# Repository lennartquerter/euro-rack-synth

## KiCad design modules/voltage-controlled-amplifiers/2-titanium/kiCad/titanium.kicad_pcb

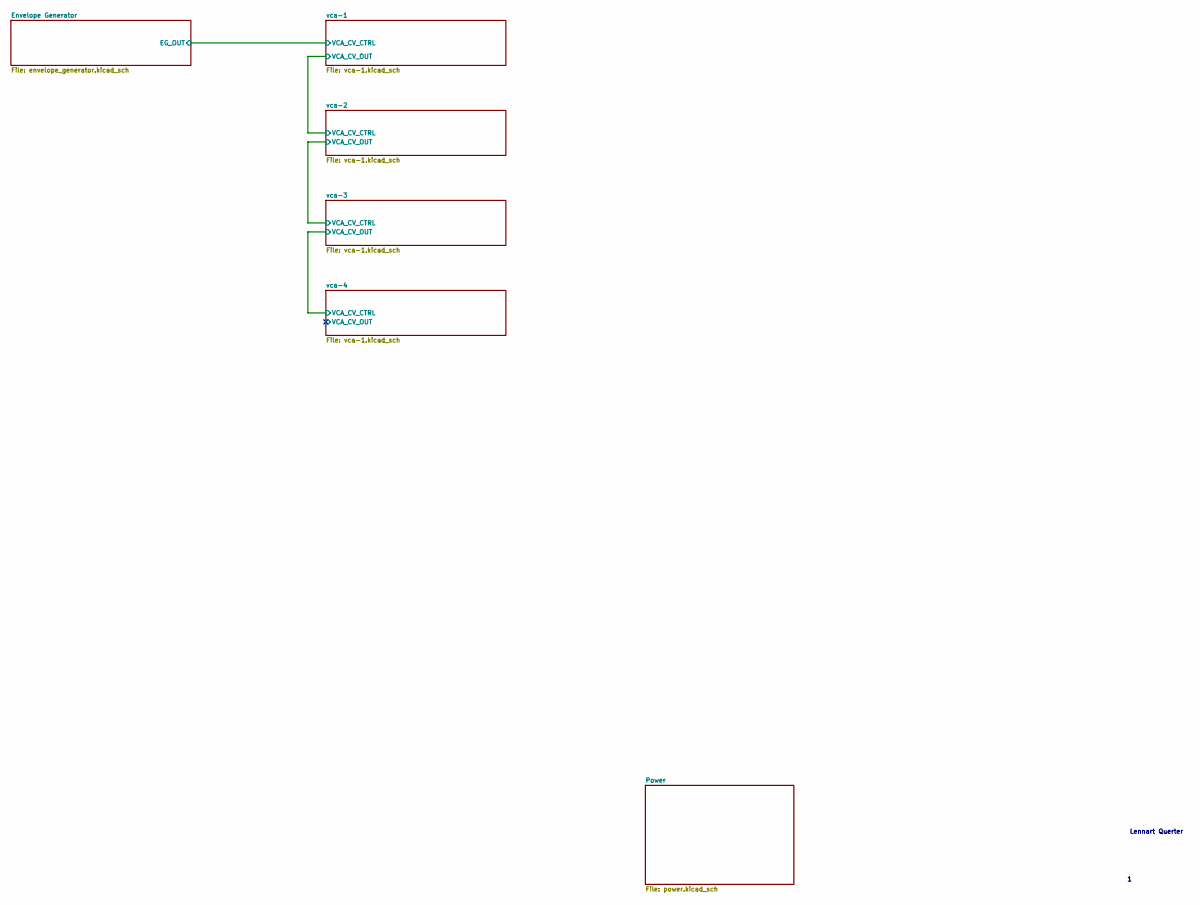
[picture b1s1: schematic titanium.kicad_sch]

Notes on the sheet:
Lennart Querter

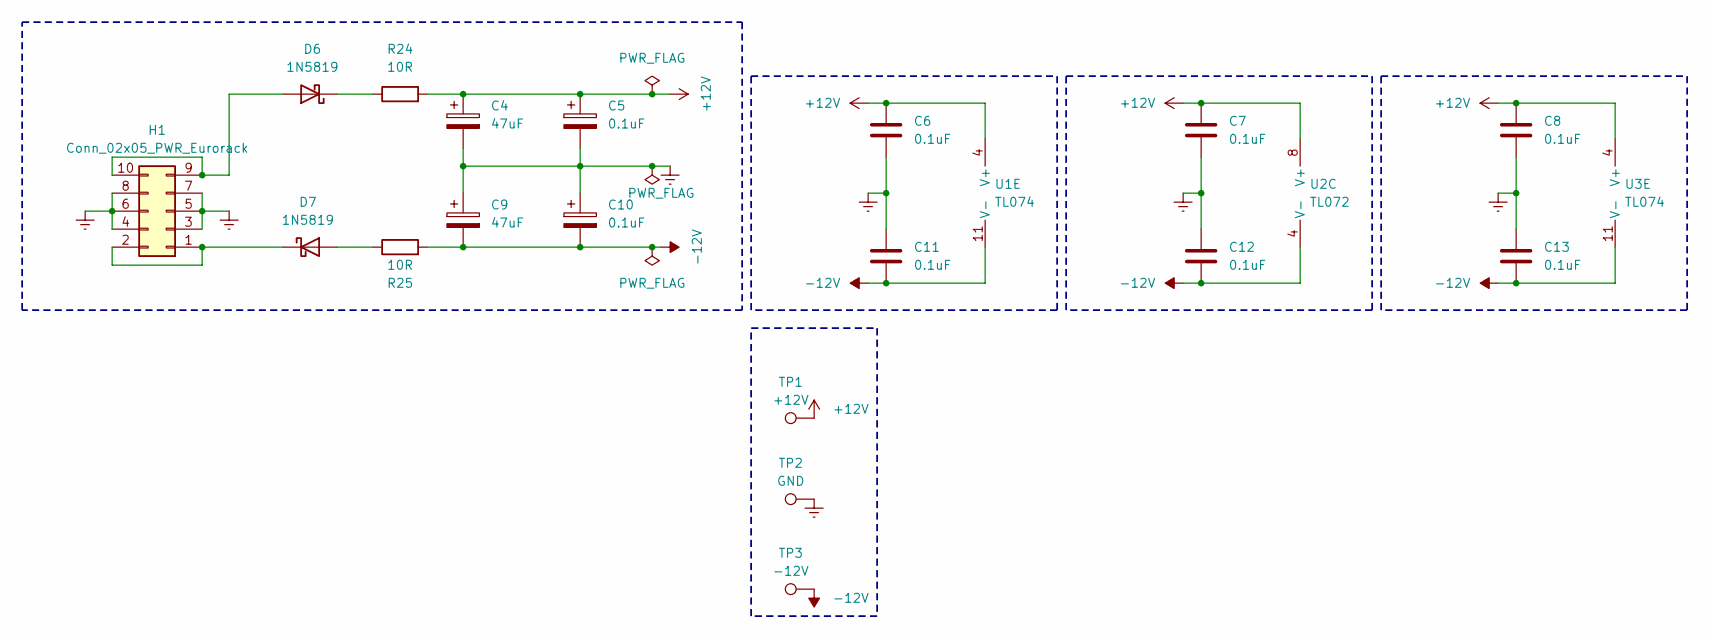
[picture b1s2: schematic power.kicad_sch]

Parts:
C4, C9: 47uF; CP_Radial_D6.3mm_P2.50mm
C5, C10: 0.1uF; CP_Radial_D4.0mm_P2.00mm
C6, C7, C8, C11, C12, C13: 0.1uF; C_0805_2012Metric_Pad1.18x1.45mm_HandSolder
D6, D7: 1N5819; D_SOD-123
H1: Conn_02x05_PWR_Eurorack; IDC-Header_2x05_P2.54mm_Vertical
R24, R25: 10R; R_0805_2012Metric_Pad1.20x1.40mm_HandSolder
TP1: +12V; Pin_D1.0mm_L10.0mm
TP2: GND; Pin_D1.0mm_L10.0mm
TP3: -12V; Pin_D1.0mm_L10.0mm
U1, U3: TL074; SOIC-14
U2: TL072; SOIC-8

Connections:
+12V: C4.1, C5.1, C6.1, C7.1, C8.1, R24.2, TP1.1, U1.4 (V+), U2.8 (V+), U3.4 (V+); also elsewhere on the board
-12V: C9.2, C10.2, C11.2, C12.2, C13.2, R25.2, TP3.1, U1.11 (V-), U2.4 (V-), U3.11 (V-); also elsewhere on the board
GNDREF: C4.2, C5.2, C6.2, C7.2, C8.2, C9.1, C10.1, C11.1, C12.1, C13.1, H1.3, H1.4, H1.5, H1.6, H1.7, H1.8, TP2.1, U1.12 (+), U3.3 (+); also elsewhere on the board
unnamed: D6.2 (A), H1.9, H1.10
unnamed: D6.1 (K), R24.1
unnamed: D7.2 (A), R25.1
unnamed: D7.1 (K), H1.1, H1.2
unnamed 64: U1.1; also elsewhere on the board
unnamed 66: U1.14; also elsewhere on the board
unnamed 70: U3.14; also elsewhere on the board
unnamed 72: U3.1; also elsewhere on the board
unnamed 76: U1.3 (+); also elsewhere on the board
unnamed 77: U1.2 (-); also elsewhere on the board
unnamed 81: U1.13 (-); also elsewhere on the board
unnamed 83: U3.2 (-); also elsewhere on the board
unnamed 87: U3.12 (+); also elsewhere on the board
unnamed 88: U3.13 (-); also elsewhere on the board

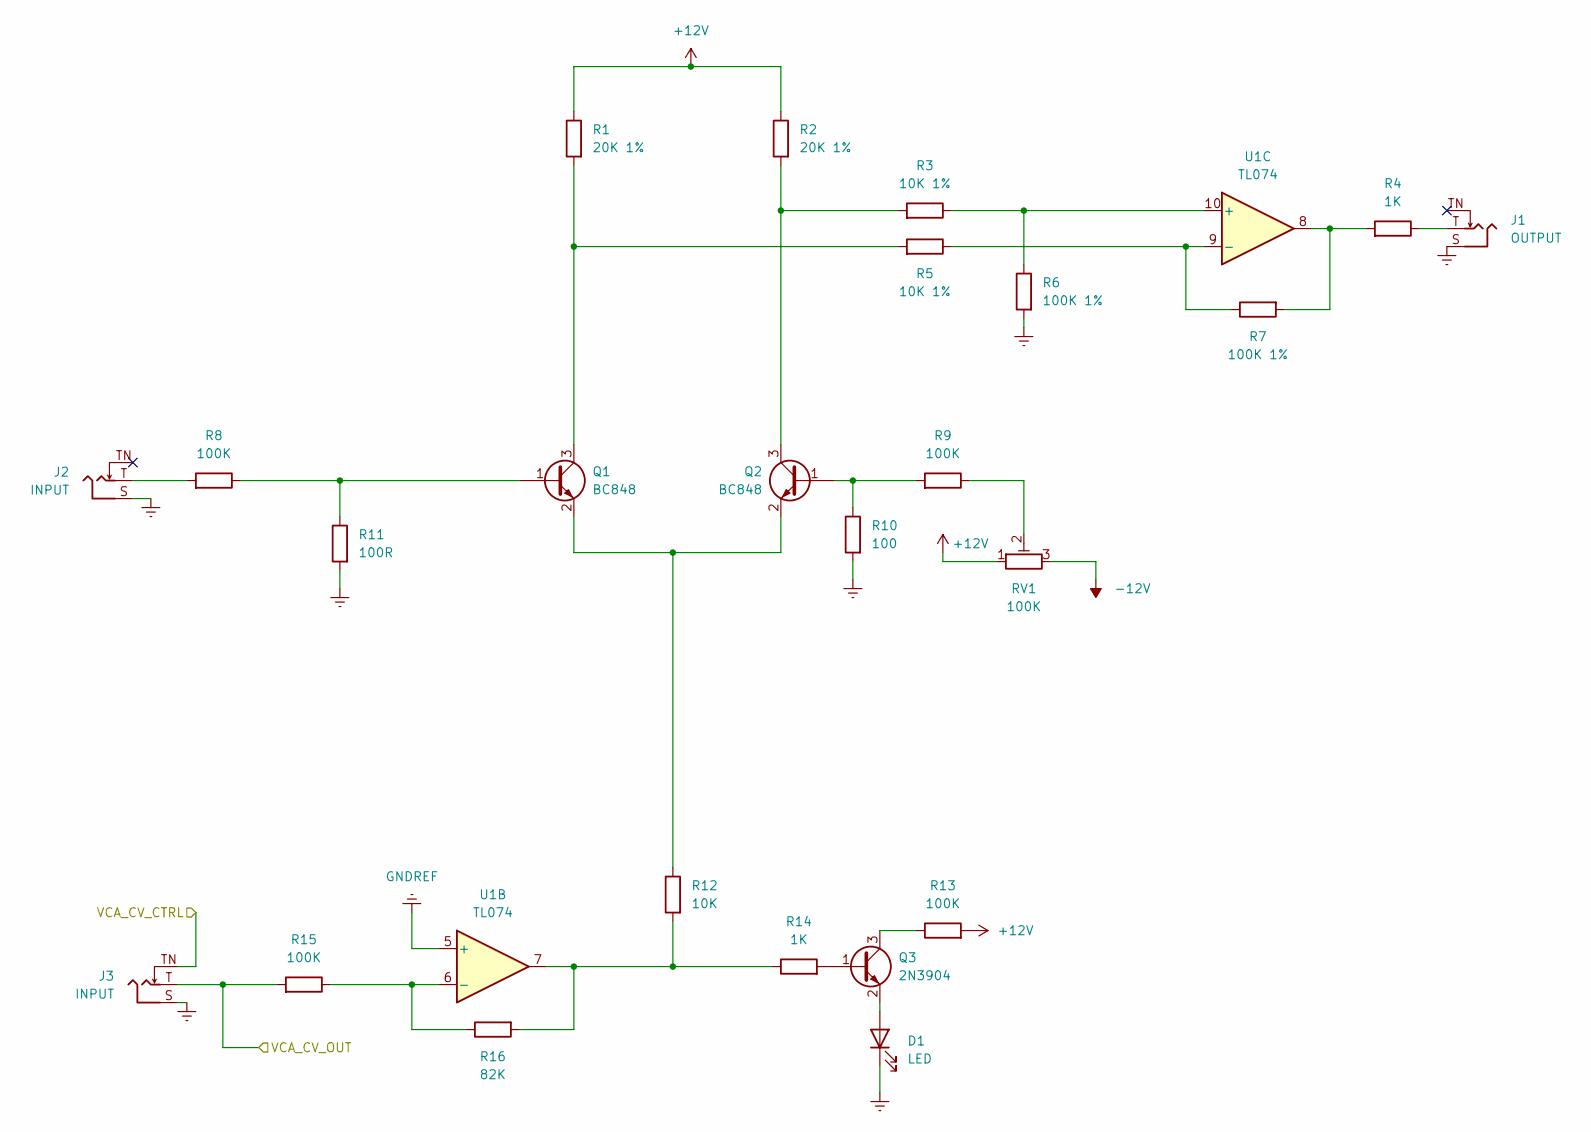
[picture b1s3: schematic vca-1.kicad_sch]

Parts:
D1: LED; LED_D3.0mm
J1: OUTPUT; Jack_3.5mm_QingPu_WQP-PJ398SM_Vertical_CircularHoles
J2, J3: INPUT; Jack_3.5mm_QingPu_WQP-PJ398SM_Vertical_CircularHoles
Q1, Q2: BC848; SOT-23_Handsoldering
Q3: 2N3904; SOT-23_Handsoldering
R1, R2: 20K 1%; R_0805_2012Metric_Pad1.20x1.40mm_HandSolder
R3, R5: 10K 1%; R_0805_2012Metric_Pad1.20x1.40mm_HandSolder
R4, R14: 1K; R_0805_2012Metric_Pad1.20x1.40mm_HandSolder
R6, R7: 100K 1%; R_0805_2012Metric_Pad1.20x1.40mm_HandSolder
R8, R9, R13, R15: 100K; R_0805_2012Metric_Pad1.20x1.40mm_HandSolder
R10: 100; R_0805_2012Metric_Pad1.20x1.40mm_HandSolder
R11: 100R; R_0805_2012Metric_Pad1.20x1.40mm_HandSolder
R12: 10K; R_0805_2012Metric_Pad1.20x1.40mm_HandSolder
R16: 82K; R_0805_2012Metric_Pad1.20x1.40mm_HandSolder
RV1: 100K; Potentiometer_Piher_PT-6-V_Vertical
U1: TL074; SOIC-14

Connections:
+12V: R1.2, R2.2, R13.2, RV1.1; also elsewhere on the board
-12V: RV1.3; also elsewhere on the board
/Envelope Generator/EG_OUT: J3.TN; also elsewhere on the board
/vca-1/VCA_CV_OUT: J3.T, R15.1; also elsewhere on the board
GNDREF: D1.1 (K), J1.S, J2.S, J3.S, R6.1, R10.1, R11.1, U1.5 (+), U1.12 (+); also elsewhere on the board
unnamed: D1.2 (A), Q3.2 (E)
unnamed: J1.T, R4.2
unnamed: J2.T, R8.1
unnamed: Q1.1 (B), R8.2, R11.2
unnamed: Q1.3 (C), R1.1, R5.1
unnamed: Q1.2 (E), Q2.2 (E), R12.2
unnamed: Q2.1 (B), R9.1, R10.2
unnamed: Q2.3 (C), R2.1, R3.1
unnamed: Q3.1 (B), R14.2
unnamed: Q3.3 (C), R13.1
unnamed: R4.1, R7.1, U1.8
unnamed: R9.2, RV1.2
unnamed: R12.1, R14.1, R16.1, U1.7
unnamed 64: U1.1; also elsewhere on the board
unnamed 66: U1.14; also elsewhere on the board
unnamed 76: U1.3 (+); also elsewhere on the board
unnamed 77: U1.2 (-); also elsewhere on the board
unnamed: R15.2, R16.2, U1.6 (-)
unnamed: R3.2, R6.2, U1.10 (+)
unnamed: R5.2, R7.2, U1.9 (-)
unnamed 81: U1.13 (-); also elsewhere on the board

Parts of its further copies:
D8, D9, D10: LED; LED_D3.0mm
J6, J9, J12: OUTPUT; Jack_3.5mm_QingPu_WQP-PJ398SM_Vertical_CircularHoles
J7, J8, J10, J11, J13, J14: INPUT; Jack_3.5mm_QingPu_WQP-PJ398SM_Vertical_CircularHoles
Q5, Q6, Q8, Q9, Q11, Q12: BC848; SOT-23_Handsoldering
Q7, Q10, Q13: 2N3904; SOT-23_Handsoldering
R26, R27, R42, R43, R58, R59: 20K 1%; R_0805_2012Metric_Pad1.20x1.40mm_HandSolder
R28, R30, R44, R46, R60, R62: 10K 1%; R_0805_2012Metric_Pad1.20x1.40mm_HandSolder
R29, R39, R45, R55, R61, R71: 1K; R_0805_2012Metric_Pad1.20x1.40mm_HandSolder
R31, R32, R47, R48, R63, R64: 100K 1%; R_0805_2012Metric_Pad1.20x1.40mm_HandSolder
R33, R34, R38, R40, R49, R50, R54, R56, R65, R66, R70, R72: 100K; R_0805_2012Metric_Pad1.20x1.40mm_HandSolder
R35, R51, R67: 100; R_0805_2012Metric_Pad1.20x1.40mm_HandSolder
R36, R52, R68: 100R; R_0805_2012Metric_Pad1.20x1.40mm_HandSolder
R37, R53, R69: 10K; R_0805_2012Metric_Pad1.20x1.40mm_HandSolder
R41, R57, R73: 82K; R_0805_2012Metric_Pad1.20x1.40mm_HandSolder
RV2, RV3, RV4: 100K; Potentiometer_Piher_PT-6-V_Vertical

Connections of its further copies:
+12V: R26.2, R27.2, R38.2, R42.2, R43.2, R54.2, R58.2, R59.2, R70.2, RV2.1, RV3.1, RV4.1; also elsewhere on the board
-12V: RV2.3, RV3.3, RV4.3; also elsewhere on the board
/vca-1/VCA_CV_OUT: J8.TN; also elsewhere on the board
/vca-2/VCA_CV_OUT: J8.T, J11.TN, R40.1
/vca-3/VCA_CV_OUT: J11.T, J14.TN, R56.1
/vca-4/VCA_CV_OUT: J14.T, R72.1
GNDREF: D8.1 (K), D9.1 (K), D10.1 (K), J6.S, J7.S, J8.S, J9.S, J10.S, J11.S, J12.S, J13.S, J14.S, R31.1, R35.1, R36.1, R47.1, R51.1, R52.1, R63.1, R67.1, R68.1; also elsewhere on the board
unnamed: D8.2 (A), Q7.2 (E)
unnamed: D9.2 (A), Q10.2 (E)
unnamed: D10.2 (A), Q13.2 (E)
unnamed: J6.T, R29.2
unnamed: J7.T, R33.1
unnamed: J9.T, R45.2
unnamed: J10.T, R49.1
unnamed: J12.T, R61.2
unnamed: J13.T, R65.1
unnamed: Q5.1 (B), R33.2, R36.2
unnamed: Q5.3 (C), R26.1, R30.1
unnamed: Q5.2 (E), Q6.2 (E), R37.2
unnamed: Q6.1 (B), R34.1, R35.2
unnamed: Q6.3 (C), R27.1, R28.1
unnamed: Q7.1 (B), R39.2
unnamed: Q7.3 (C), R38.1
unnamed: Q8.1 (B), R49.2, R52.2
unnamed: Q8.3 (C), R42.1, R46.1
unnamed: Q8.2 (E), Q9.2 (E), R53.2
unnamed: Q9.1 (B), R50.1, R51.2
unnamed: Q9.3 (C), R43.1, R44.1
unnamed: Q10.1 (B), R55.2
unnamed: Q10.3 (C), R54.1
unnamed: Q11.1 (B), R65.2, R68.2
unnamed: Q11.3 (C), R58.1, R62.1
unnamed: Q11.2 (E), Q12.2 (E), R69.2
unnamed: Q12.1 (B), R66.1, R67.2
unnamed: Q12.3 (C), R59.1, R60.1
unnamed: Q13.1 (B), R71.2
unnamed: Q13.3 (C), R70.1
unnamed 64: R29.1, R32.1; also elsewhere on the board
unnamed: R34.2, RV2.2
unnamed 66: R37.1, R39.1, R41.1; also elsewhere on the board
unnamed 67: R45.1, R48.1; also elsewhere on the board
unnamed: R50.2, RV3.2
unnamed 69: R53.1, R55.1, R57.1; also elsewhere on the board
unnamed 70: R61.1, R64.1; also elsewhere on the board
unnamed: R66.2, RV4.2
unnamed 72: R69.1, R71.1, R73.1; also elsewhere on the board
unnamed 76: R28.2, R31.2; also elsewhere on the board
unnamed 77: R30.2, R32.2; also elsewhere on the board
unnamed 81: R40.2, R41.2; also elsewhere on the board
unnamed 83: R72.2, R73.2; also elsewhere on the board
unnamed 84: R56.2, R57.2; also elsewhere on the board
unnamed 85: R44.2, R47.2; also elsewhere on the board
unnamed 86: R46.2, R48.2; also elsewhere on the board
unnamed 87: R60.2, R63.2; also elsewhere on the board
unnamed 88: R62.2, R64.2; also elsewhere on the board

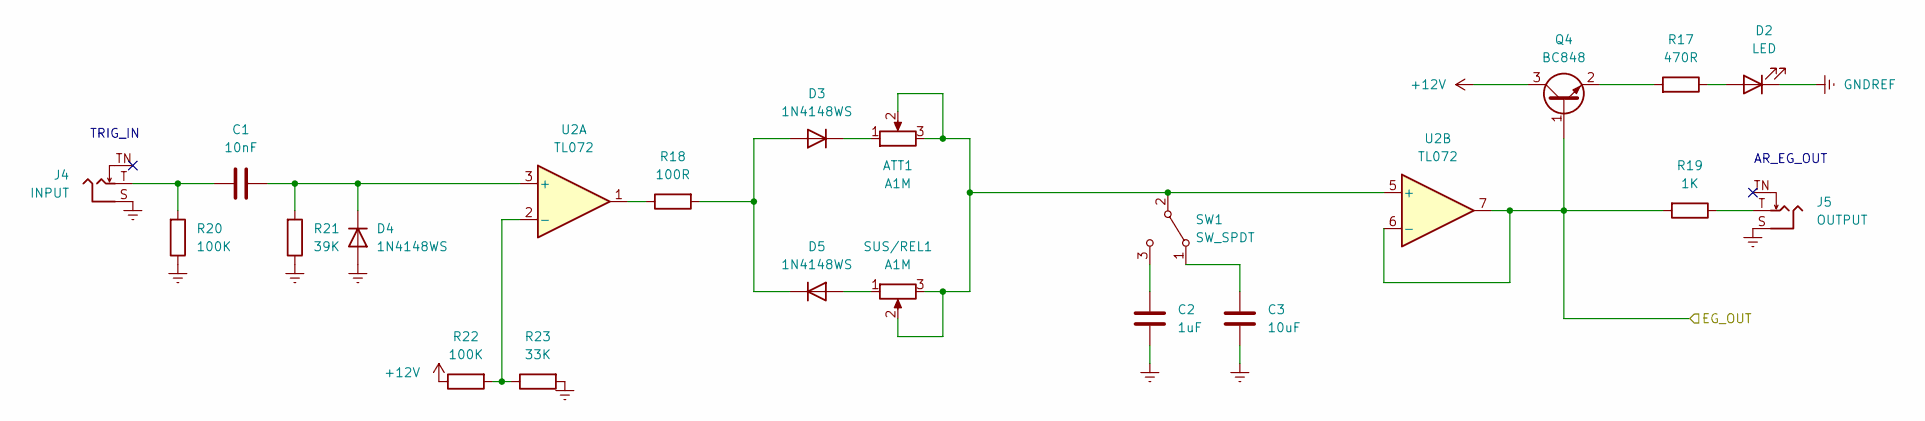
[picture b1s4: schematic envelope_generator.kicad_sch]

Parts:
ATT1: A1M; Potentiometer_TT_P0915N
C1: 10nF; C_0805_2012Metric_Pad1.18x1.45mm_HandSolder
C2: 1uF; C_RECT_WIMA_0.1uF
C3: 10uF; C_RECT_MKT_1uF
D2: LED; LED_D3.0mm
D3, D4, D5: 1N4148WS; D_SOD-323_HandSoldering
J4: INPUT; Jack_3.5mm_QingPu_WQP-PJ398SM_Vertical_CircularHoles
J5: OUTPUT; Jack_3.5mm_QingPu_WQP-PJ398SM_Vertical_CircularHoles
Q4: BC848; SOT-23_Handsoldering
R17: 470R; R_0805_2012Metric_Pad1.20x1.40mm_HandSolder
R18: 100R; R_0805_2012Metric_Pad1.20x1.40mm_HandSolder
R19: 1K; R_0805_2012Metric_Pad1.20x1.40mm_HandSolder
R20, R22: 100K; R_0805_2012Metric_Pad1.20x1.40mm_HandSolder
R21: 39K; R_0805_2012Metric_Pad1.20x1.40mm_HandSolder
R23: 33K; R_0805_2012Metric_Pad1.20x1.40mm_HandSolder
SUS/REL1: A1M; Potentiometer_TT_P0915N
SW1: SW_SPDT; SW_default
U2: TL072; SOIC-8

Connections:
+12V: Q4.3 (C), R22.2; also elsewhere on the board
/Envelope Generator/EG_OUT: Q4.1 (B), R19.1, U2.6 (-), U2.7; also elsewhere on the board
GNDREF: C2.2, C3.2, D2.1 (K), D4.2 (A), J4.S, J5.S, R20.2, R21.2, R23.1; also elsewhere on the board
unnamed: C1.1, J4.T, R20.1
unnamed: D2.2 (A), R17.2
unnamed: D3.2 (A), D5.1 (K), R18.1
unnamed: ATT1.1, D3.1 (K)
unnamed: C1.2, D4.1 (K), R21.1, U2.3 (+)
unnamed: D5.2 (A), SUS/REL1.1
unnamed: J5.T, R19.2
unnamed: Q4.2 (E), R17.1
unnamed: R18.2, U2.1
unnamed: C3.1, SW1.1 (A)
unnamed: ATT1.2, ATT1.3, SUS/REL1.2, SUS/REL1.3, SW1.2 (B), U2.5 (+)
unnamed: C2.1, SW1.3 (C)
unnamed: R22.1, R23.2, U2.2 (-)

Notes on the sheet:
AR_EG_OUT
TRIG_IN

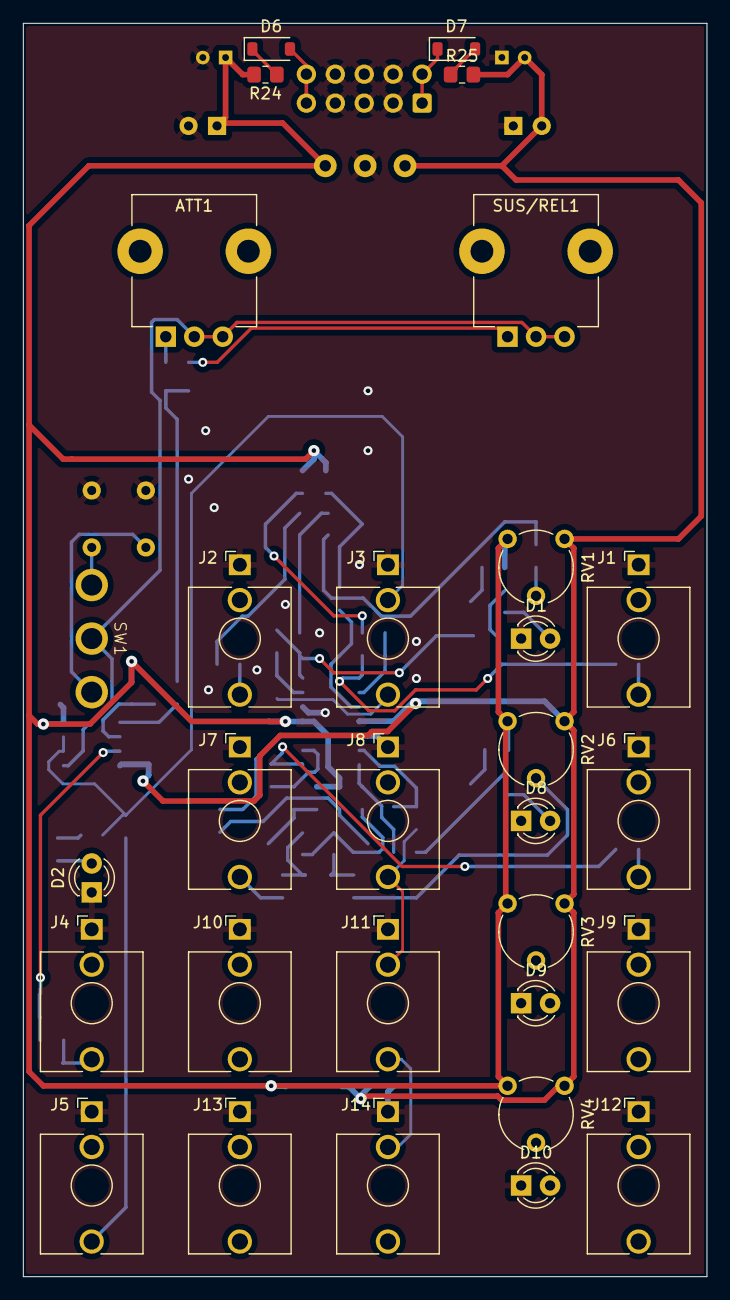
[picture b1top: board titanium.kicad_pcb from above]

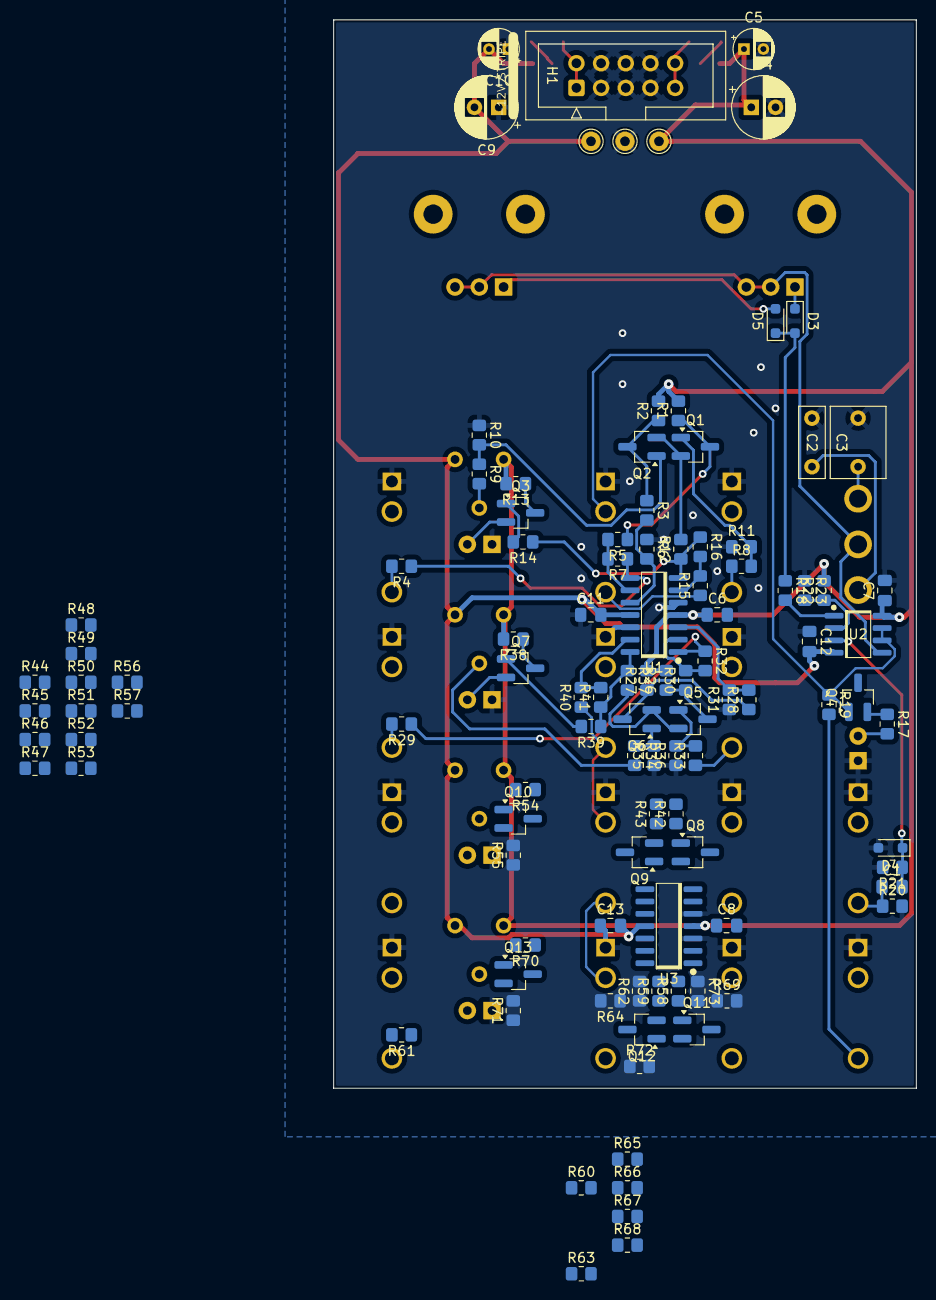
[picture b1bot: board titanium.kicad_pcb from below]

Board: 2 copper layers, 60.0 x 110.0 mm, 137 parts (107 on the bottom side), 89 nets.

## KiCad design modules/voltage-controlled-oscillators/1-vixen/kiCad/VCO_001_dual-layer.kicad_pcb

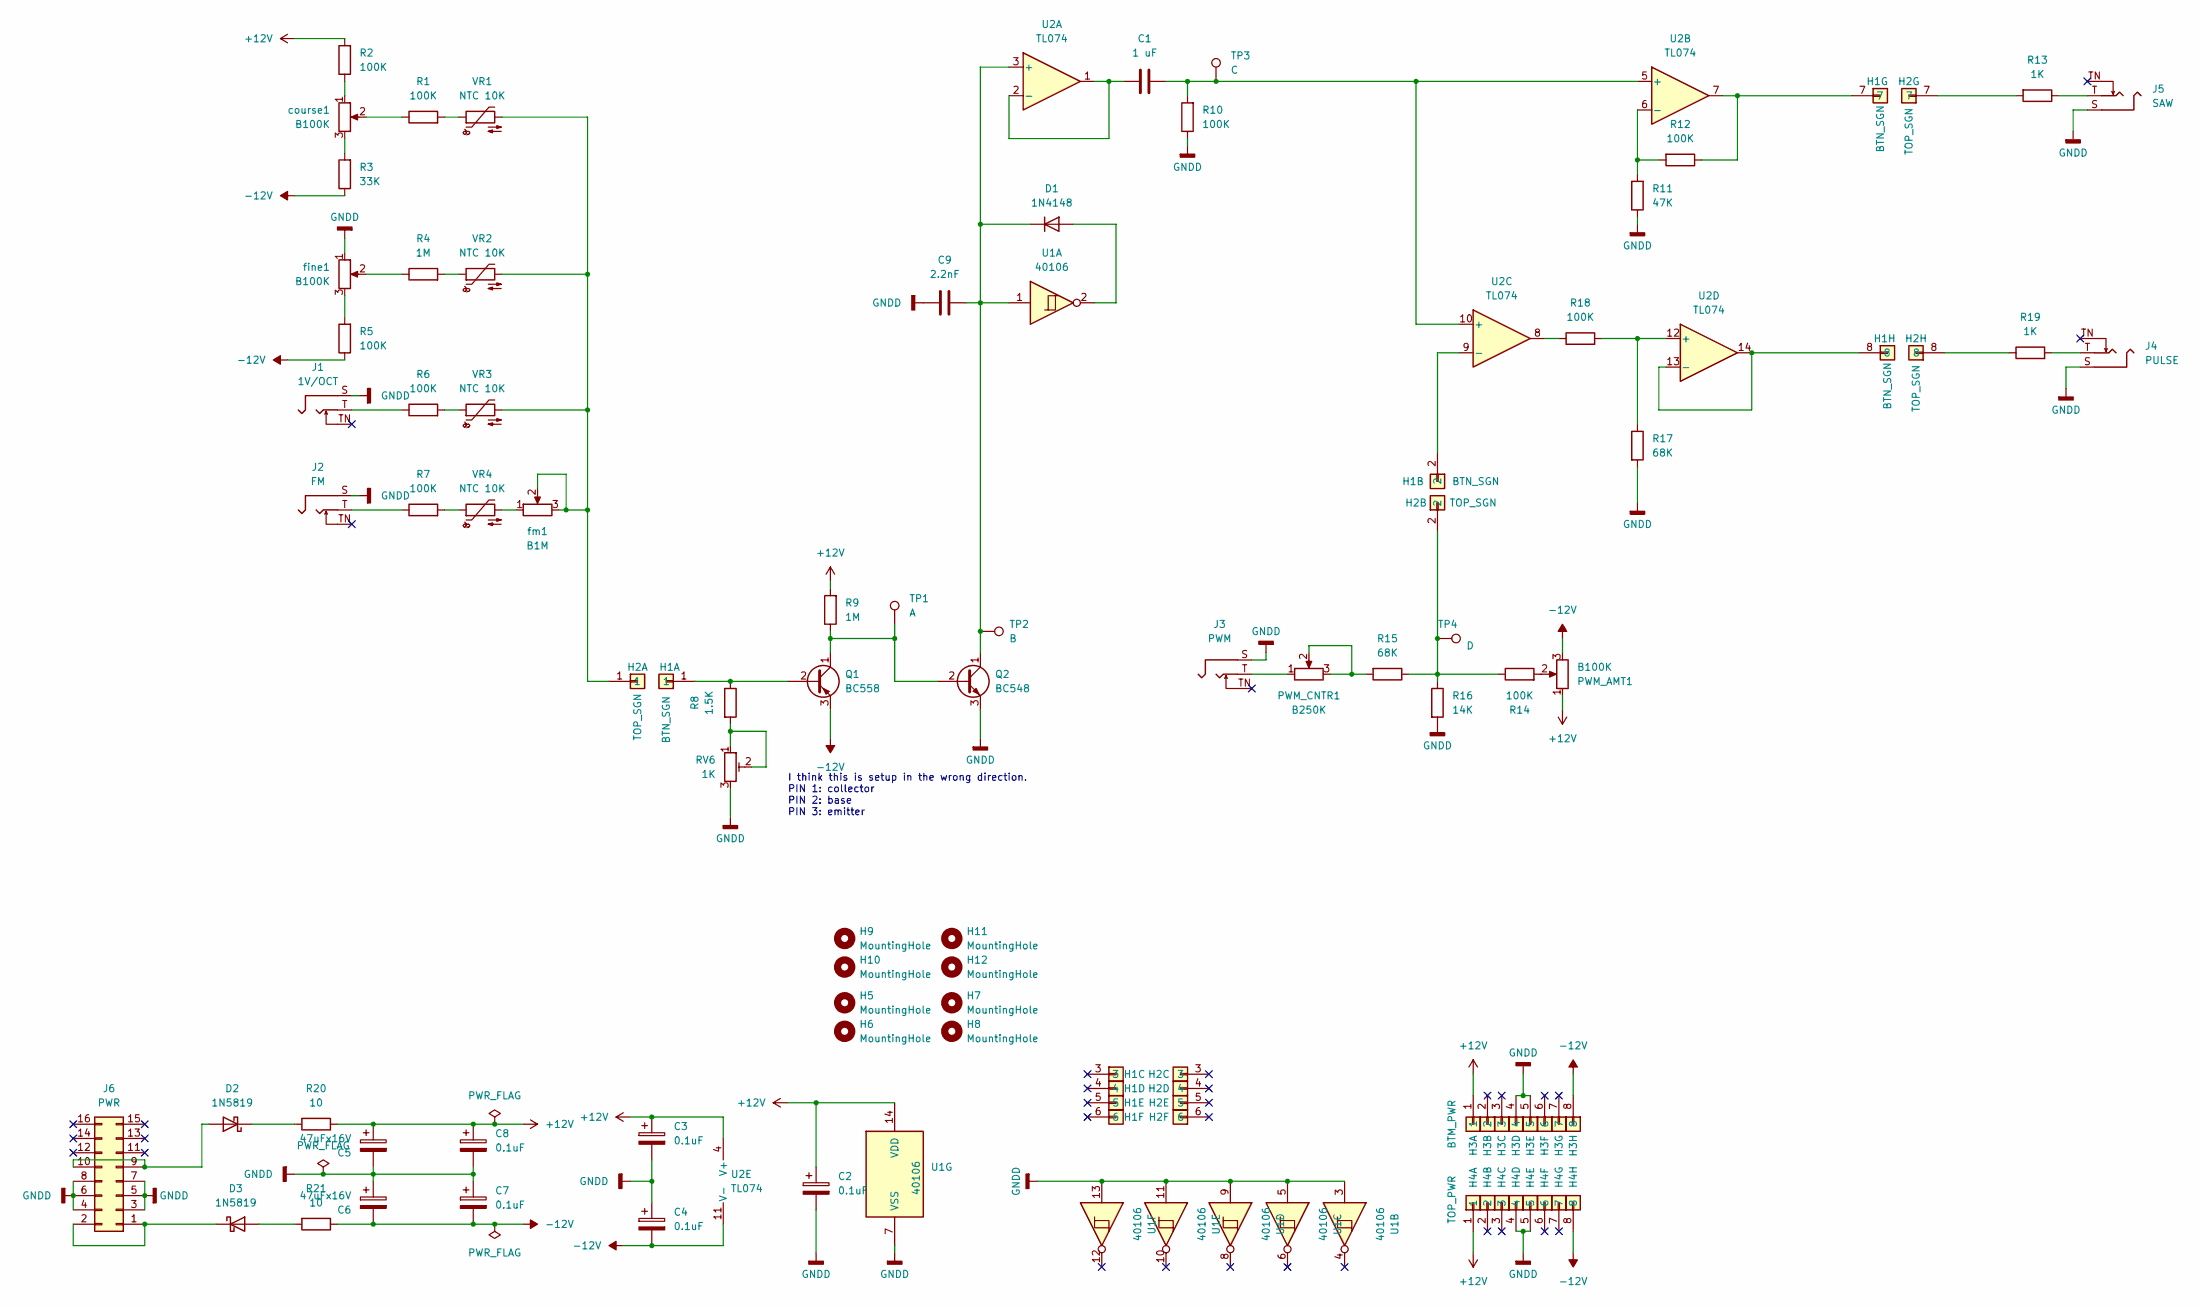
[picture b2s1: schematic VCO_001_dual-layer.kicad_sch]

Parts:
C1: 1 uF; C_RECT_MKT_1uF
C2, C3, C4, C7, C8: 0.1uF; CP_Radial_D4.0mm_P2.00mm
C5, C6: 47uFx16V; CP_Radial_D5.0mm_P2.00mm
C9: 2.2nF; C_RECT_WIMA_0.1uF
D1: 1N4148; D_DO-35_SOD27_P7.62mm_Horizontal
D2, D3: 1N5819; D_DO-35_SOD27_P7.62mm_Horizontal
H1: BTN_SGN; PinSocket_1x08_P2.00mm_Vertical
H2: TOP_SGN; PinHeader_1x08_P2.00mm_Vertical
H3: BTM_PWR; PinSocket_1x08_P2.00mm_Vertical
H4: TOP_PWR; PinHeader_1x08_P2.00mm_Vertical
H5, H6, H7, H8, H9, H10, H11, H12: MountingHole; MountingHole_3.5mm
J1: 1V/OCT; Jack_3.5mm_QingPu_WQP-PJ398SM_Vertical_CircularHoles
J2: FM; Jack_3.5mm_QingPu_WQP-PJ398SM_Vertical_CircularHoles
J3: PWM; Jack_3.5mm_QingPu_WQP-PJ398SM_Vertical_CircularHoles
J4: PULSE; Jack_3.5mm_QingPu_WQP-PJ398SM_Vertical_CircularHoles
J5: SAW; Jack_3.5mm_QingPu_WQP-PJ398SM_Vertical_CircularHoles
J6: PWR; CONN_02x08_PWR
PWM_AMT1: B100K; Potentiometer_TT_P0915N
PWM_CNTR1: B250K; Potentiometer_TT_P0915N
Q1: BC558; TO-92_Inline
Q2: BC548; TO-92_Inline
R1, R2, R5, R6, R7, R10, R12, R14, R18: 100K; R_Axial_DIN0207_L6.3mm_D2.5mm_P7.62mm_Horizontal
R3: 33K; R_Axial_DIN0207_L6.3mm_D2.5mm_P7.62mm_Horizontal
R4, R9: 1M; R_Axial_DIN0207_L6.3mm_D2.5mm_P7.62mm_Horizontal
R8: 1.5K; R_Axial_DIN0207_L6.3mm_D2.5mm_P7.62mm_Horizontal
R11: 47K; R_Axial_DIN0207_L6.3mm_D2.5mm_P7.62mm_Horizontal
R13, R19: 1K; R_Axial_DIN0207_L6.3mm_D2.5mm_P7.62mm_Horizontal
R15, R17: 68K; R_Axial_DIN0207_L6.3mm_D2.5mm_P7.62mm_Horizontal
R16: 14K; R_Axial_DIN0207_L6.3mm_D2.5mm_P7.62mm_Horizontal
R20, R21: 10; R_Axial_DIN0207_L6.3mm_D2.5mm_P7.62mm_Horizontal
RV6: 1K; Potentiometer_Bourns_3296W_Vertical
TP1: A; Pin_D1.0mm_L10.0mm
TP2: B; Pin_D1.0mm_L10.0mm
TP3: C; Pin_D1.0mm_L10.0mm
TP4: D; Pin_D1.0mm_L10.0mm
U1: 40106; DIP-14_W7.62mm_Socket_LongPads
U2: TL074; DIP-14_W7.62mm_Socket_LongPads
VR1, VR2, VR3, VR4: NTC 10K; R_Axial_DIN0207_L6.3mm_D2.5mm_P5.08mm_Vertical
course1: B100K; Potentiometer_TT_P0915N
fine1: B100K; Potentiometer_TT_P0915N
fm1: B1M; Potentiometer_TT_P0915N

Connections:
+12V: C2.1, C3.1, C5.1, C8.1, H3.1, H4.1, PWM_AMT1.1, R2.2, R9.2, R20.1, U1.14 (VDD), U2.4 (V+)
-12V: C4.2, C6.2, C7.2, H3.8, H4.8, PWM_AMT1.3, Q1.3 (E), R3.1, R5.1, R21.1, U2.11 (V-)
GNDD: C2.2, C3.2, C4.1, C5.2, C6.1, C7.1, C8.2, C9.2, H3.4, H3.5, H4.4, H4.5, J1.S, J2.S, J3.S, J4.S, J5.S, J6.3 (GND), J6.4 (GND), J6.5 (GND), J6.6 (GND), J6.7 (GND), J6.8 (GND), Q2.3 (E), R10.1, R11.1, R16.2, R17.2, RV6.3, U1.3, U1.5, U1.7 (VSS), U1.9, U1.11, U1.13, fine1.1
unnamed: D1.2 (A), U1.2
unnamed: C9.1, D1.1 (K), Q2.1 (C), TP2.1, U1.1, U2.3 (+)
unnamed: D2.2 (A), J6.9 (+12V), J6.10 (+12V)
unnamed: D2.1 (K), R20.2
unnamed: D3.2 (A), R21.2
unnamed: D3.1 (K), J6.1 (-12V), J6.2 (-12V)
unnamed: H1.7, R12.1, U2.7
unnamed: H2.1, VR1.2, VR2.2, VR3.2, fm1.2, fm1.3
unnamed: H2.2, R14.1, R15.1, R16.1, TP4.1
unnamed: H2.7, R13.2
unnamed: H2.8, R19.1
unnamed: J1.T, R6.1
unnamed: J2.T, R7.1
unnamed: J3.T, PWM_CNTR1.1
unnamed: J4.T, R19.2
unnamed: J5.T, R13.1
unnamed: PWM_AMT1.2, R14.2
unnamed: PWM_CNTR1.2, PWM_CNTR1.3, R15.2
unnamed: H1.1, Q1.2 (B), R8.1
unnamed: Q1.1 (C), Q2.2 (B), R9.1, TP1.1
unnamed: R1.1, course1.2
unnamed: R1.2, VR1.1
unnamed: R2.1, course1.1
unnamed: R3.2, course1.3
unnamed: R4.1, fine1.2
unnamed: R4.2, VR2.1
unnamed: R5.2, fine1.3
unnamed: R6.2, VR3.1
unnamed: R7.2, VR4.1
unnamed: R8.2, RV6.1, RV6.2
unnamed: R18.1, U2.8
unnamed: C1.1, U2.1, U2.2 (-)
unnamed: C1.2, R10.2, TP3.1, U2.5 (+), U2.10 (+)
unnamed: R11.2, R12.2, U2.6 (-)
unnamed: H1.2, U2.9 (-)
unnamed: R17.1, R18.2, U2.12 (+)
unnamed: H1.8, U2.13 (-), U2.14
unnamed: VR4.2, fm1.1

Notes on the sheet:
I think this is setup in the wrong direction. PIN 1: collector PIN 2: base PIN 3: emitter

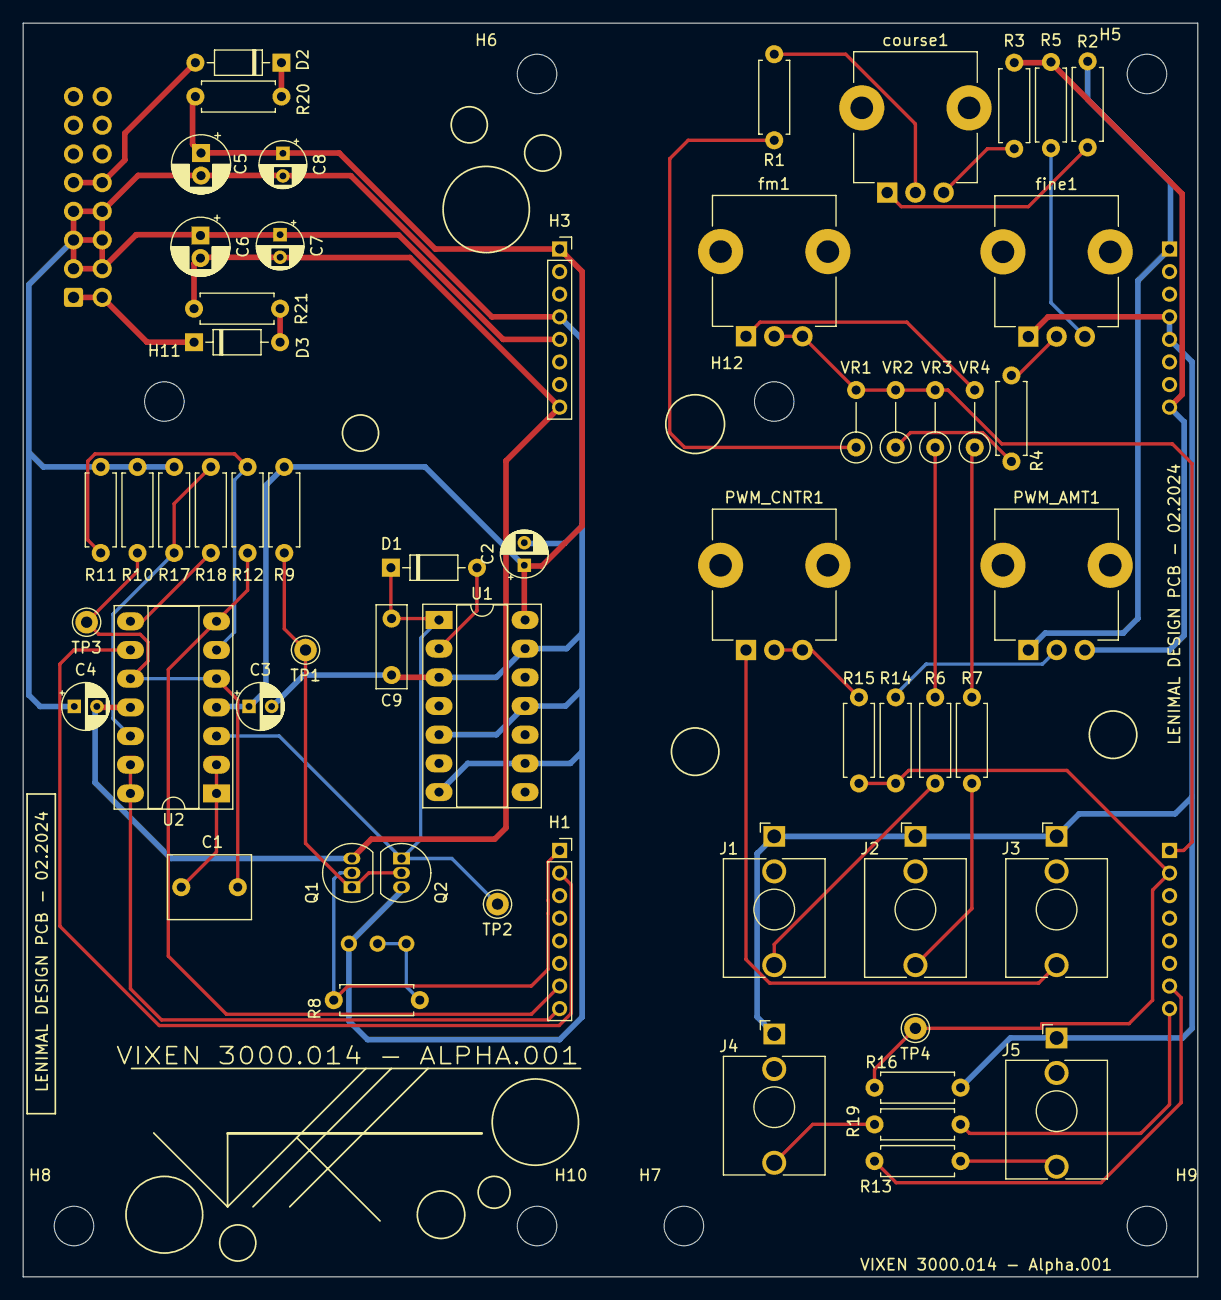
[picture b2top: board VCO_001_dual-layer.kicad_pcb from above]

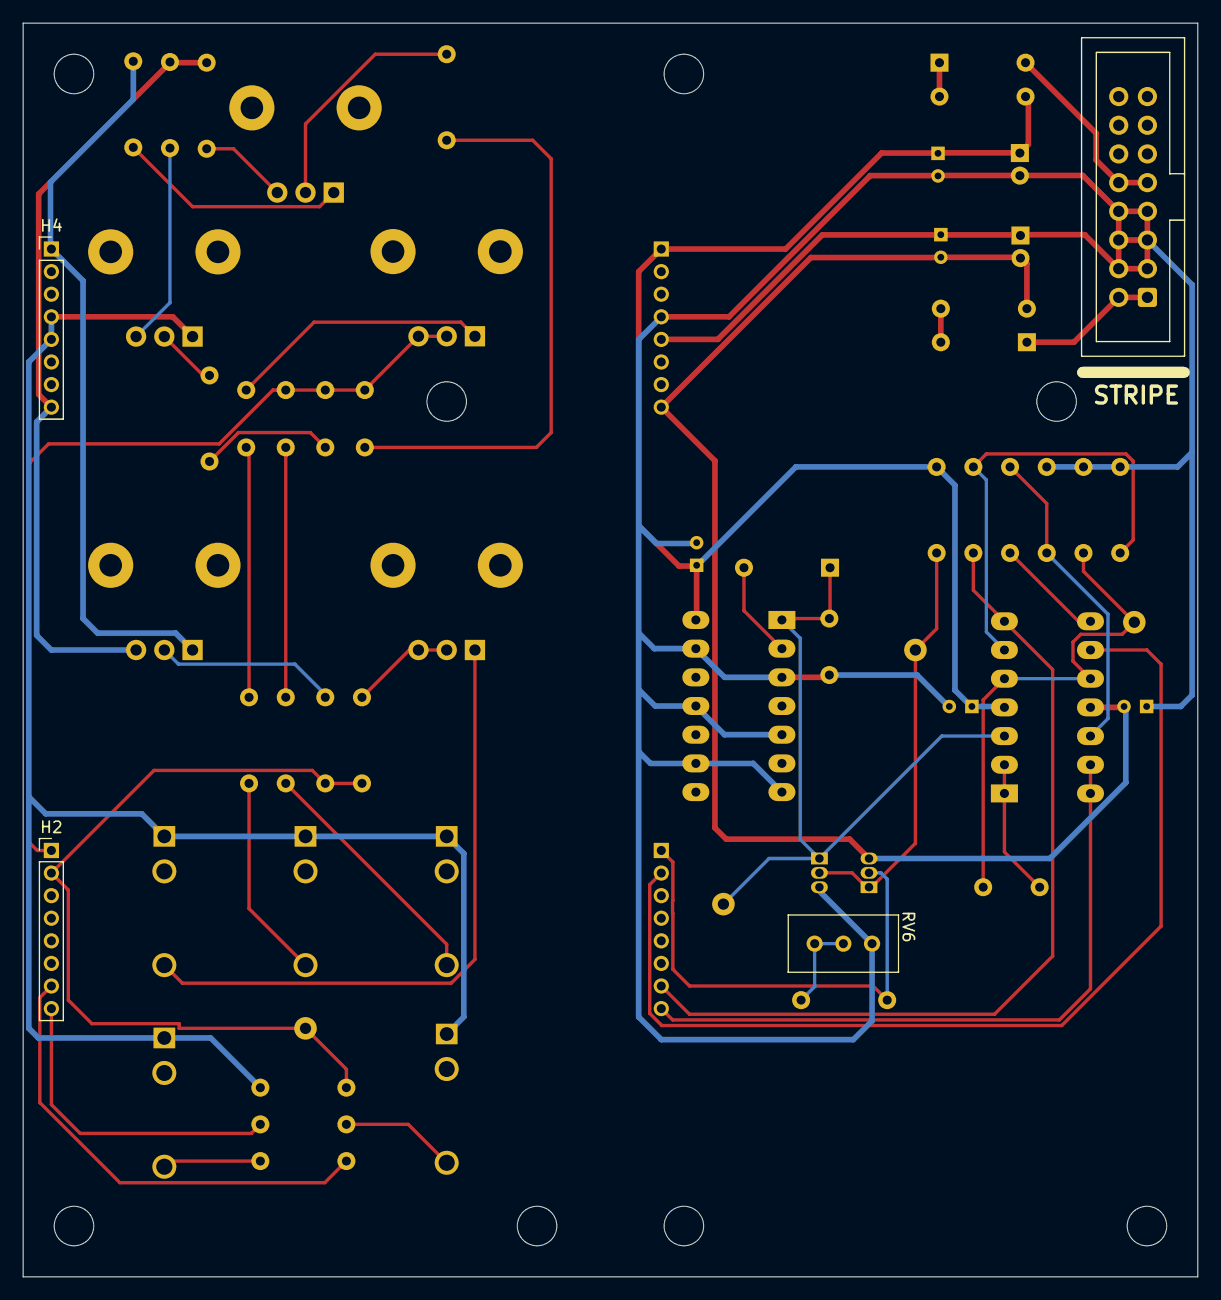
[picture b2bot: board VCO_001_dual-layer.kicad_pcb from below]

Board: 2 copper layers, 104.0 x 111.0 mm, 69 parts (4 on the bottom side), 41 nets.
